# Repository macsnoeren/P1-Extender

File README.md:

-yellow)

# P1-Extender

## Need your smart meter P1 port far away?
When you charging point is far away from your smartmeter and it needs a P1 poort connection to perform load balancing AND you are not able to use long wires? Than you can use this P1 extender. It connects with the network or Internet and read the messages from your smart meter (using another smart meter P1 reader). It provide these messages similarly to the smart meter. Just connect your charger point to this remote P1 port and it will get the P1 messages.

The hardware and software simulate a smart meter P1 port.

-- In progress

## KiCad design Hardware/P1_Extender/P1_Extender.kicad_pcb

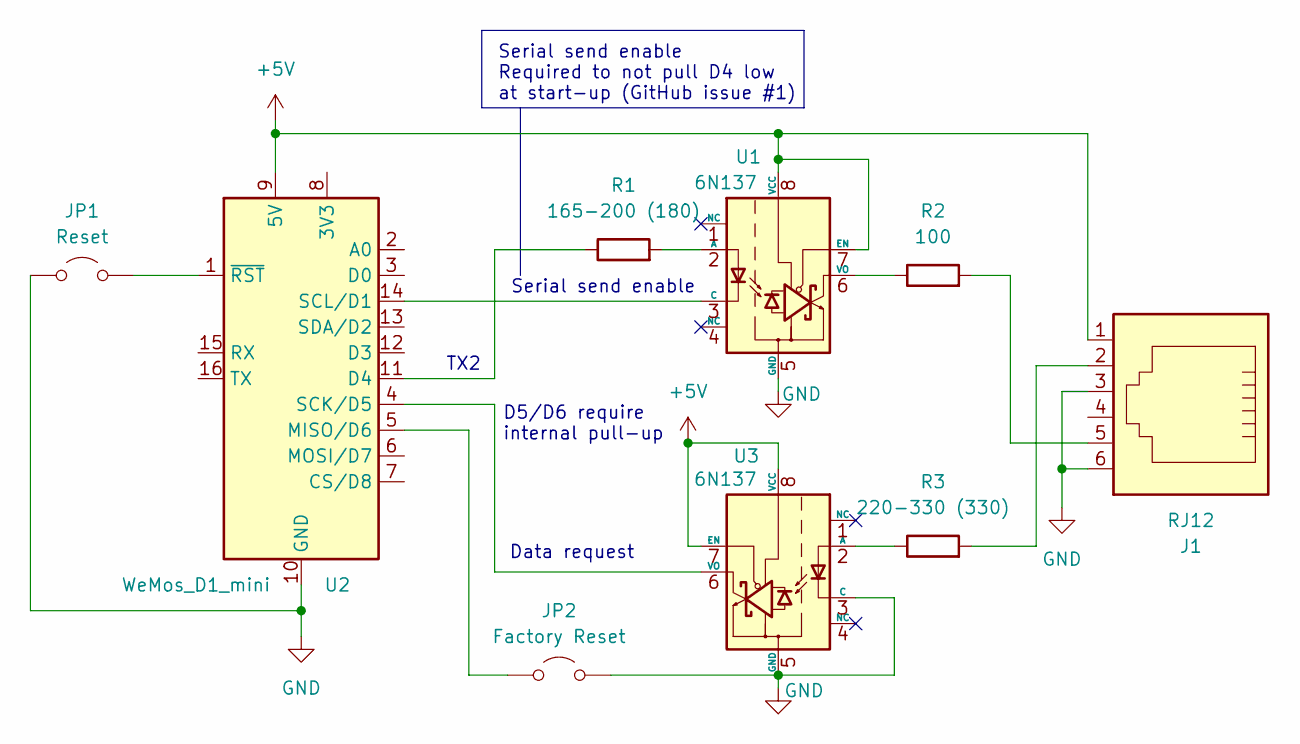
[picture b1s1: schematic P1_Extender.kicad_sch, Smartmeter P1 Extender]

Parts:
J1: RJ12; RJ12_Amphenol_54601-x06_Horizontal
JP1: Reset; PinHeader_1x02_P2.54mm_Vertical
JP2: Factory Reset; PinHeader_1x02_P2.54mm_Vertical
R1: 165-200 (180); R_Axial_DIN0207_L6.3mm_D2.5mm_P10.16mm_Horizontal
R2: 100; R_Axial_DIN0207_L6.3mm_D2.5mm_P10.16mm_Horizontal
R3: 220-330 (330); R_Axial_DIN0207_L6.3mm_D2.5mm_P10.16mm_Horizontal
U1, U3: 6N137; DIP-8_W7.62mm
U2: WeMos_D1_mini; WEMOS_D1_mini_light

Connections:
+5V: J1.1, U1.7 (EN), U1.8 (VCC), U2.9 (5V), U3.7 (EN), U3.8 (VCC)
GND: J1.3, J1.6, JP1.1 (A), JP2.2 (B), U1.5 (GND), U2.10 (GND), U3.3 (C), U3.5 (GND)
unnamed: J1.2, R3.2
unnamed: J1.5, R2.2
unnamed: JP1.2 (B), U2.1 (~RST)
unnamed: JP2.1 (A), U2.5 (MISO/D6)
unnamed: R1.2, U1.2 (A)
unnamed: U1.3 (C), U2.14 (SCL/D1)
unnamed: R2.1, U1.6 (VO)
unnamed: R1.1, U2.11 (D4)
unnamed: U2.4 (SCK/D5), U3.6 (VO)
unnamed: R3.1, U3.2 (A)

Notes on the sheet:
TX2
Serial send enable Required to not pull D4 low at start-up (GitHub issue #1)
Data request
Serial send enable
D5/D6 require internal pull-up

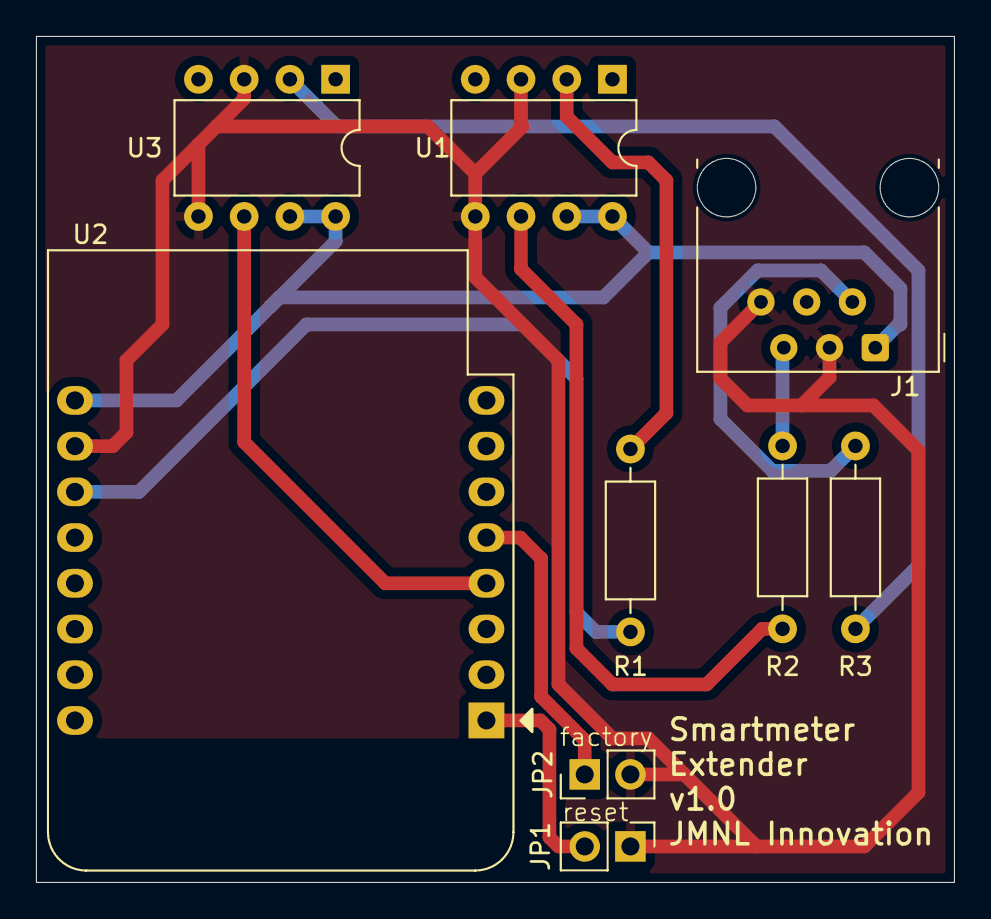
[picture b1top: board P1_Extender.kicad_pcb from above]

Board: 2 copper layers, 51.0 x 47.0 mm, 9 parts (0 on the bottom side), 12 nets.

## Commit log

2025-01-11 Initial commit containing the hardware version 1.0
2025-01-11 Initial readme for the project
2025-01-12 Typo fixed.
2025-01-26 Added a draft version of the firmware and soldering documentation
2025-01-26 Fixed pull-up for D5 and added data request logic
2025-01-26 Added new hardware version to fix the issues
2025-01-26 Added factory default and serial send enable functionality
2025-01-26 Changed to version 1.1 testing
2025-01-26 Changed picture to version 1.1
2025-01-27 Added first MQTT functionality
2025-01-27 First connection with the MQTT broker
2025-02-01 First working version
2025-08-12 Added logo file
